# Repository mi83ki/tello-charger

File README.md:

<!-- omit in toc -->
# Tello Charger

小型ドローンTelloの自動充電を可能にする装置です。

<!-- omit in toc -->
## 目次

- [1. Tello Chargerとは](#1-tello-chargerとは)
- [2. 製作するために必要なデータ](#2-製作するために必要なデータ)
  - [2.1. 3Dデータ](#21-3dデータ)
  - [2.2. 回路図](#22-回路図)
  - [2.3. ソースコード](#23-ソースコード)
    - [2.3.1. 開発環境の構築](#231-開発環境の構築)
      - [2.3.1.1. VSCodeのインストール](#2311-vscodeのインストール)
      - [2.3.1.2. PlatformIOのインストール](#2312-platformioのインストール)
    - [2.3.2. 初期設定](#232-初期設定)
      - [2.3.2.1. サブモジュールの取得](#2321-サブモジュールの取得)
      - [2.3.2.2. ssid.hの作成](#2322-ssidhの作成)
    - [2.3.3. ソフトウェアの書き込み](#233-ソフトウェアの書き込み)
      - [2.3.3.1. ワークスペースを開く](#2331-ワークスペースを開く)
      - [2.3.3.2. ビルド](#2332-ビルド)
      - [2.3.3.3. 書き込み](#2333-書き込み)
- [3. WebAPI仕様](#3-webapi仕様)
- [4. 概要設計書](#4-概要設計書)

## 1. Tello Chargerとは

Tello EDUの自動充電装置です。

以下はドローンにUSBコネクタを接続する機構の動画です。

以下はドローンを自動充電する一連動作の動画です。

## 2. 製作するために必要なデータ

製作するために必要なデータを以下に説明します。

### 2.1. 3Dデータ

3Dデータ（STEP）は`step/`ディレクトリに保存しています。\
STLデータ等に変換し、3Dプリンタで印刷します。\
3Dデータの品番リストは[概要設計書](doc/design/design.md)を参照してください。

### 2.2. 回路図

回路図（Eegleデータ）は`eagle/`ディレクトリに保存しています。\
必要な部品を購入し、ユニバーサル基板で手はんだします。\
必要な部品のリストは[概要設計書](doc/design/design.md)を参照してください。

### 2.3. ソースコード

ATOM Liteに書き込むソースコードは`src/`ディレクトリに保存しています。

#### 2.3.1. 開発環境の構築

##### 2.3.1.1. VSCodeのインストール

Arduinoマイコンへの書き込みも可能なエディタとしてVSCodeを推奨する。\
以下のURLに従ってVSCodeをインストールする。\
<https://miya-system-works.com/blog/detail/vscode-install/>

##### 2.3.1.2. PlatformIOのインストール

以下URLを参考に、VSCodeの拡張機能であるPlatformIOをインストールする。\
<https://zenn.dev/kotaproj/articles/esp32_vscode_pio>

#### 2.3.2. 初期設定

初回に必要な作業を記載します。

##### 2.3.2.1. サブモジュールの取得

以下のコマンドでサブモジュールを取得する必要があります。

~~~bash
git submodule update --init
~~~

##### 2.3.2.2. ssid.hの作成

WiFiの接続先SSIDとパスワードは以下の手順で設定します。

1. 「src/TelloCharger/src/」フォルダの「ssid_example.h」を同じフォルダにコピーして「ssid.h」に名称変更する

2. 「ssid.h」の各項目を自分の環境に合わせて変更する

    ~~~h
    /**
     * @file ssid_example.h
     * @brief SSID情報を記述するヘッダファイルの例
     *
     * @details 環境に合わせて、ファイル名をssid.hにリネームして利用してください（ssid.hはgitignoreされている）
     */

    #pragma once

    #define WIFI_SSID "XXXXXXXXXXX"
    #define WIFI_PASSWORD "XXXXXXXX"

    /** 固定IPアドレス（"MY_FIXED_IP_1"."MY_FIXED_IP_2"."MY_FIXED_IP_3"."MY_FIXED_IP_4"） */
    #define MY_FIXED_IP_1 (192)
    #define MY_FIXED_IP_2 (168)
    #define MY_FIXED_IP_3 (1)
    #define MY_FIXED_IP_4 (12)

    /** ゲートウェイのIPアドレス（"MY_FIXED_IP_1"."MY_FIXED_IP_2"."MY_FIXED_IP_3"."GATEWAY_IP_4"） */
    #define GATEWAY_IP_4 (1)
    ~~~

#### 2.3.3. ソフトウェアの書き込み

##### 2.3.3.1. ワークスペースを開く

「xsa-cloud/xsa-cloud.code-workspace」をダブルクリックしてVSCodeで開く。

##### 2.3.3.2. ビルド

左下の`✓`ボタンを押下する。

##### 2.3.3.3. 書き込み

クナイデバイスをUSBケーブルでPCに接続し、左下の`→`ボタンを押下する。

## 3. WebAPI仕様

TelloChargerは上位システムからWebAPIで制御します。\
以下のAPI仕様を参照してください。

[Tello Charger API](doc/openapi/api.html)

## 4. 概要設計書

概要設計内容は以下を参照してください。

[概要設計書](doc/design/design.md)

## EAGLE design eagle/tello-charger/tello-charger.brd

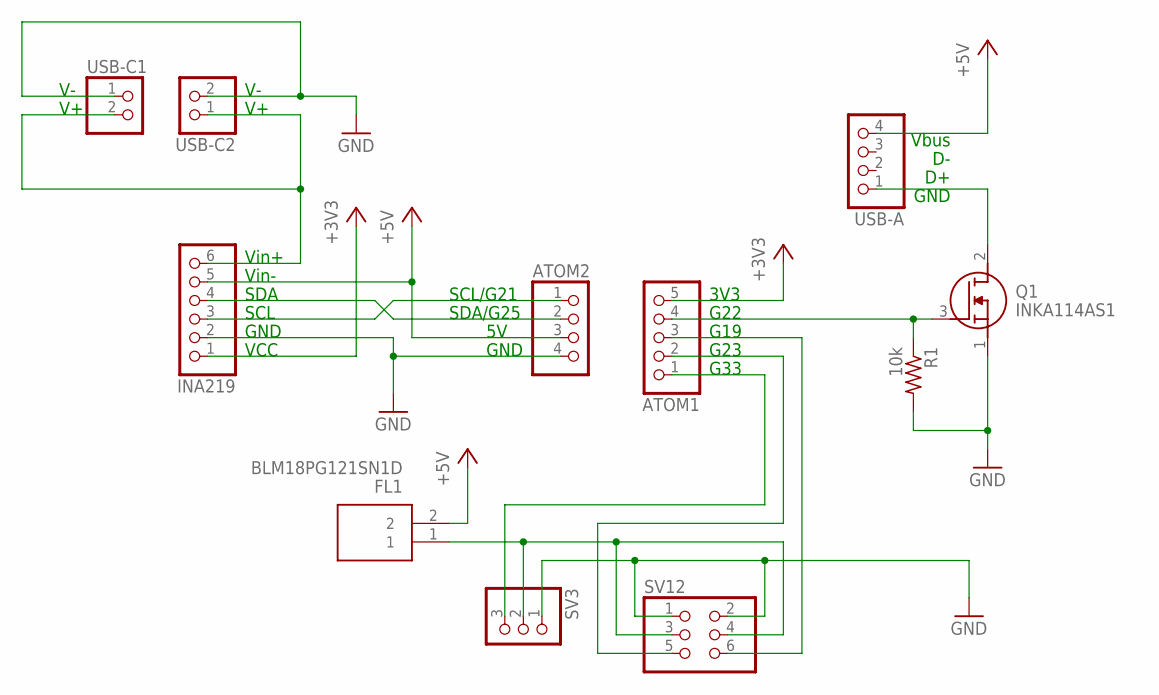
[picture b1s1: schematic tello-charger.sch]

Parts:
ATOM1: PINHD-1X5; 1X05
ATOM2: PINHD-1X4; 1X04
FL1: BLM18PG121SN1D; BLM18AG102BH1D
INA219: PINHD-1X6; 1X06
Q1: INKA114AS1
R1: 10k; R0603
SV3: PINHD-1X3/90; 1X03/90
SV12: PINHD-2X3/90; 2X03/90
USB-A: PINHD-1X4; 1X04
USB-C1, USB-C2: PINHD-1X2; 1X02

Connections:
+3V3: ATOM1.5, INA219.1
+5V: ATOM2.3, FL1.2, INA219.5, USB-A.4
GND: ATOM2.4, INA219.2, Q1.1 (S), R1.2, SV3.1, SV12.1, SV12.2, USB-C1.1, USB-C2.2
unnamed: INA219.6, USB-C1.2, USB-C2.1
unnamed: Q1.2 (D), USB-A.1
unnamed: ATOM2.2, INA219.4
unnamed: ATOM2.1, INA219.3
unnamed: ATOM1.2, SV12.5
unnamed: ATOM1.4, Q1.3 (G), R1.1
unnamed: FL1.1, SV3.2, SV12.3, SV12.4
unnamed: ATOM1.3, SV12.6
unnamed: ATOM1.1, SV3.3

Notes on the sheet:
3V3
G22
G19
G23
G33
SCL/G21
SDA/G25
GND
Vin+
Vin-
SDA
SCL
VCC
Vbus

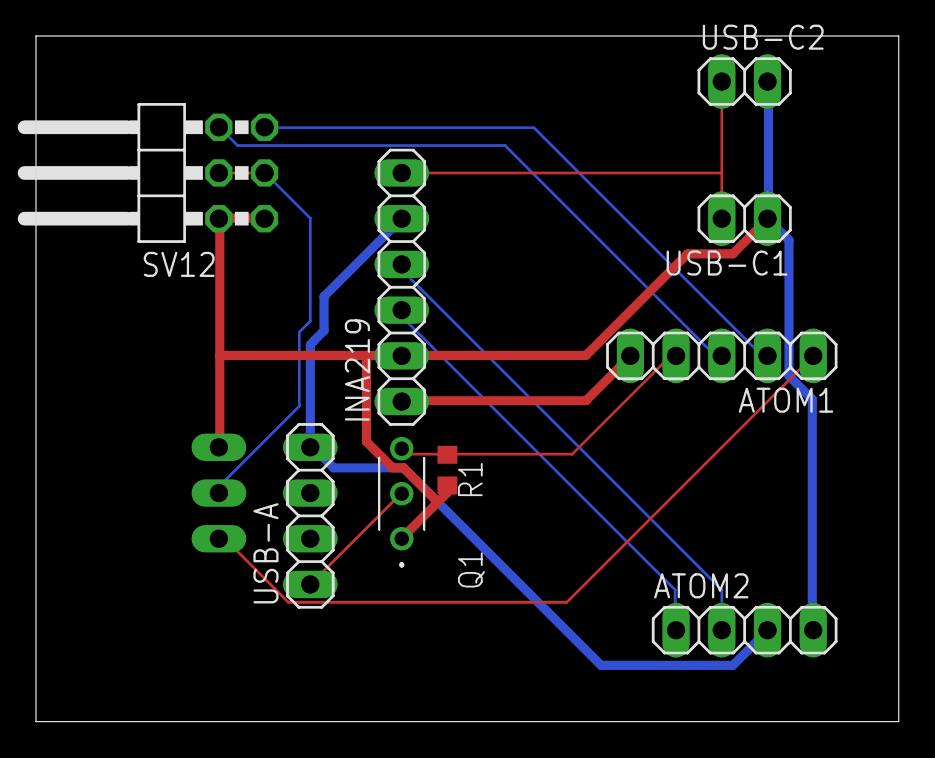
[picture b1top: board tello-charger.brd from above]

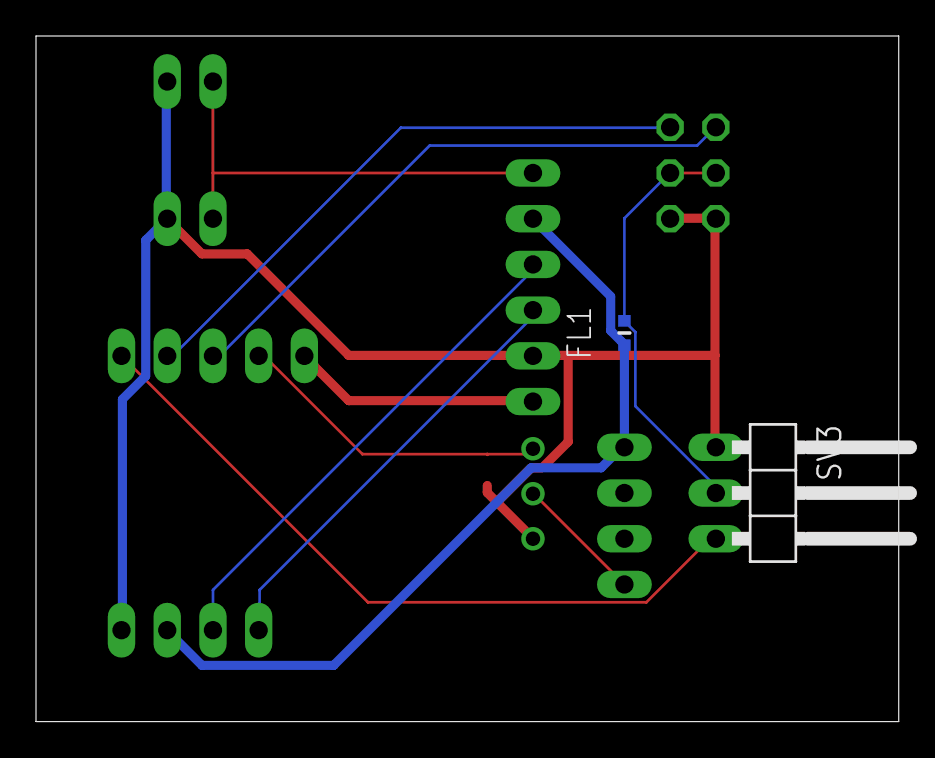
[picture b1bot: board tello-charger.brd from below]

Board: 2 copper layers, 47.9 x 38.1 mm, 11 parts (2 on the bottom side), 12 nets.

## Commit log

2023-03-18 [gitignore] Add gitignore file
2023-03-18 [README] Add README
2023-03-18 [doc][memo] Add memo
2023-03-18 [TelloCharger] Add project of PlatformIO
2023-03-18 [doc] Add design doc
2023-03-18 Add VSCode workspase
2023-03-25 [lib] Add submodule ArduinoCommon
2023-03-25 [doc][memo] Add submodule ArduinoCommon
2023-03-25 [gitignore] Add eagle ignore files
2023-03-25 [eagle] Add schematic
2023-03-25 [doc][design] Update block diagram
2023-03-26 [eagle] Update schematic
2023-03-26 [doc][design] Add schematic and pcb layout
2023-03-26 [submodule] Update ArduinoCommon
2023-03-26 [TelloCharger] Change to use ServoESP32 of ArduinoCommon
2023-04-14 [README] Update Readme
2023-04-14 [src] Add MOSFET control
2023-04-14 [eagle] Add PDF of schematic and board
2023-05-05 [workspace] Add formatter settings
2023-05-06 [TelloCharger] Add HTTP API
2023-05-06 [doc][memo] Add HTTP API specification
2023-05-06 [TelloCharger] Add ChargeController and FETController
2023-05-06 [doc] Add design diaglams
2023-05-06 [TelloCharger] Add ChargeManager
2023-05-06 [TelloCharger] Add charge time for api response
2023-05-07 [TelloCharger] Add process to wait for response
2023-05-12 [TelloCharger] Update CATCH_CNT
2023-05-14 [TelloCharger] Add retry charge
2023-05-14 [TelloCharger] Add example of ssid.h
2023-05-15 [TelloCharger] Add charger status
2023-05-16 [doc] Change API specification of power on
2023-05-16 [TelloCharger] Change power on api
2023-08-18 [TelloCharger] Update ArduinoCommon library
2023-08-18 [TelloCharger] Change power on time to 2sec from 1sec
2023-09-23 [TelloCharger] Add reading current
2023-09-23 [TelloCharger] Change formatter setting
2023-09-23 [TelloCharger] Add auto stop charging by current
2023-10-08 [TelloCharger] Add fixed IP setting
2023-10-08 [TelloCharger] Fixed start charge process with no current
2023-10-08 [TelloCharger] Adjust current threashold
2023-11-18 [TelloCharger] Check servo motor current
2023-11-18 [TelloCharger] Refactoring of charging controller
2023-11-19 [TelloCharger] Support for static IP addresses
2023-11-22 [doc] Update module structure
2023-11-22 [TelloCharger] Add logic to detect overcurrent and stop servo motor
2023-11-22 [Tello Charger] Change default position of arm
2024-01-12 Create LICENSE
2024-05-06 [step] Add 3D data
2024-05-06 [doc] Update design.md
2024-05-06 [README] Update README.md
2024-05-06 [gitignore] Add ignore files for Node.js
2024-05-06 Create openapi html file
2024-05-06 [README] Update READEM.md
2025-04-26 fix: update MY_FIXED_IP_4 value
    ssid_example.hのMY_FIXED_IP_4の値を12から110に変更しました。
2025-05-02 [Arduino Common] Update ArduinoCommon
2025-05-02 Add MQTT communication specification and diagram
    - Created a new SVG diagram illustrating the MQTT architecture.
    - Added a comprehensive MQTT communication specification document detailing broker settings, topic definitions, and payload structures.
    - Included revision history and purpose sections in the specification for better clarity and tracking.
2025-05-02 fix: update subproject commit reference in ArduinoCommon
    ArduinoCommonのサブプロジェクトのコミット参照を78eceb7から95d029cに更新しました。
2025-05-02 fix: update subproject commit reference in ArduinoCommon
    ArduinoCommonのサブプロジェクトのコミットリファレンスを更新しました。
2025-05-02 fix: remove timestamp from payload examples in mqtt_interface.md
    mqtt_interface.mdのペイロード例からtimestampフィールドを削除しました。
2025-05-02 feat: enhance charge controller and add message builder
    - platformio.ini: 環境設定を整理し、依存ライブラリを更新
    - ChargeController.cpp: 充電時間を秒単位で取得するメソッドを追加し、不要なピン定義を削除
    - ChargeController.h: 充電時間を秒で取得するメソッドの宣言を追加
    - CurrentReader.cpp: I2C通信の初期化を修正し、ログ出力を追加
    - MessageBuilder.cpp: 充電状態をJSON形式で生成する関数を追加
    - MessageBuilder.h: JSON生成関数の宣言を追加
2025-05-02 fix: update charging time retrieval in HttpServer
    HttpServer.cppの_onChargeGetメソッドで、充電時間の取得をミリ秒から秒に変更しました。
2025-05-03 fix: update subproject commit reference in ArduinoCommon ArduinoCommonのサブプロジェクトのコミット参照を更新しました。
2025-05-03 feat: implement DroneCharger MQTT protocol and message handling
    新しいファイル DroneChargerProtocol.cpp と DroneChargerProtocol.h を追加し、充電状態やリクエスト・レスポンスの構造体を定義しました。また、MQTT メッセージの送受信を管理する MqttHandler クラスを実装しました。MessageBuilder 関連の古いファイルを削除し、main.cpp での MQTT ハンドラの初期化を追加しました。
2025-05-03 feat: update platformio.ini and main.cpp for improved configuration
    platformio.iniの[env:m5stack-atom]および[env:m5stack-atoms3]セクションで、build_flagsを共通の設定から拡張するように変更しました。また、main.cppから不要なArduino.hのインクルードを削除し、M5Unified.hのインクルードを整理しました。さらに、taskWifi関数内のvTaskDelayの位置を調整しました。tel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
2025-05-03 fix: update subproject commit reference in ArduinoCommon
    ArduinoCommonのサブプロジェクトのコミット参照を更新しました。
